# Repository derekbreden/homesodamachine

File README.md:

# Home Soda Machine

A kitchen appliance that dispenses real Pepsi-made diet soda — Diet Mountain Dew, Diet Pepsi, Pepsi Zero Sugar — cold and carbonated, from a faucet. Turn the handle, soda comes out.

The public face of the project is **[homesodamachine.com](https://homesodamachine.com)** — what this is, the 3D viewer, and a single signup form to be notified when units are available. This repository is the working substrate behind that.

The prototype that proves the dispense path is in Derek's kitchen today — a Lilium under-counter carbonator with peristaltic pumps injecting flavor concentrate into the dispensed water. The project's biography lives in [`biography/`](/biography/) — [`2026-04-05.md`](/biography/2026-04-05.md) (origin story: failed SodaStream, the business-license wall, the AI design wall) and [`2026-05-23.md`](/biography/2026-05-23.md) (vision into work: welding, marketing, the engineering).

The product under development is an integrated under-counter soda machine — custom-fabricated 316L stainless carbonator, harvested ice-maker refrigeration loop, foam-insulated cold core, two flavor reservoirs, all behind a single 120 VAC cord and one CO2 line. The machine as it stands, subsystem by subsystem: [`hardware/README.md`](/hardware/README.md). Where it is going and what done looks like: [`future/README.md`](/future/README.md). Who it is for: [`marketing/target-market.md`](/marketing/target-market.md); the cabinet it has to fit: [`marketing/install-envelope.md`](/marketing/install-envelope.md).

## What's where

| Path | Contents |
|---|---|
| [`biography/`](/biography/) | Project biography by chapter — `2026-04-05.md` (founding), `2026-05-23.md` (vision into work) |
| [`hardware/`](/hardware/) | The integrated soda machine under development — CAD scripts, [`bom.md`](/hardware/ledger/bom.md), [`purchases.md`](/hardware/ledger/purchases.md), [`assembly/`](/hardware/assembly/) procedures, printed parts, wiring schedules |
| [`firmware/`](/firmware/) | ESP32 + ESP32-S3 firmware: the main board, the machine display and the faucet display of the soda machine under development, the bare-board bench rig, and the weld rotator — see [`firmware/README.md`](/firmware/README.md) for which tree runs where. |
| [`web/`](/web/) | homesodamachine.com — Node server, CAD viewer — see [`web/README.md`](/web/README.md) |
| [`ios/`](/ios/) | iOS companion app: the BLE link to a machine, firmware updates, pictures, mix, care and settings |
| [`brand/`](brand/README.md) | On tap faucet identity, Big Blue palette, app icons, wordmarks, and shared asset generation |
| [`marketing/`](/marketing/) | Target market analysis, [Lincoln sales and installation](marketing/lincoln/README.md), unboxing brief, video scripts |
| [`business/`](/business/) | Incorporation, regulatory (UL 943, ASSE 1022) |
| [`future/`](/future/) | Where the project is going — the vision and the plan in [`README.md`](/future/README.md), and the desires not yet committed to plans in [`pie-in-the-sky/`](/future/pie-in-the-sky/) |
| [`tools/`](/tools/) | [The `hsm` kernel, build and geometry queries](tools/hsm/README.md), render scripts, printer and bench utilities |

Agents and collaborators landing in this repo: [`CLAUDE.md`](/CLAUDE.md) is the entry point.

## License

MIT

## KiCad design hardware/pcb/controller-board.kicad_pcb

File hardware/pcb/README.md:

# Main board

The main board is a **full PCBA**: JLCPCB-assembled SMD silicon with
through-hole field connectors, no plug-in modules. It lives in
[`pcba/`](/hardware/pcb/pcba/) — `pcba.tsx` is the board, built in
[tscircuit](https://tscircuit.com); see
[`pcba/README.md`](/hardware/pcb/pcba/README.md) for the toolchain and the
render/verify loop.

`pcba.tsx` is the **canonical source of truth for the pin map** — the ESP32 GPIO
assignments and the MCP23017 I²C bank usage (which MCP / port drives which valves
+ condenser fan, and reads which reeds). Those choices are layout-driven and the
board is what gets fabricated, so the wiring diagrams are **derived views kept in
sync with the board**, not the other way round:

- [`esp32-pinout.mmd`](/hardware/wiring/esp32-pinout.mmd) — the ESP32 GPIO map
  (a view of the board).
- [`valve-control.mmd`](/hardware/wiring/valve-control.mmd) — the MCP23017 I²C
  banks (0x20/0x21) and the valve / reed / condenser-fan wiring (a view of the
  board).
- [`ac-wiring-schedule.md`](/hardware/wiring/ac-wiring-schedule.md) — the
  run-by-run field-harness schedule (its own concern, not derived from the pin map).
- [`power.mmd`](/hardware/wiring/power.mmd) — the power topology (likewise).

"Canonical" here means *the single source everyone derives from* — not a claim the
pins are bring-up-validated (they are provisional until the board is tested). A pin
change lands in `pcba.tsx` first, then propagates to these views.

The explicit [`repo-tools check pinmap`](/tools/hsm/repo-tools/src/integrity.rs) reading compares the
canonical pin map from `pcba.tsx` and fails if `esp32-pinout.mmd`, the GPIO constants
of the assembly documents' Rust program, or the BOM disagree — a board pin missing from
the docs, a document's GPIO on the wrong role, or an electrical BOM part with no pad
(the failure that left the piezo buzzer and the MQ-6 gas sensor wired to nothing). Run `repo-tools check pinmap` when reviewing a pin change or preparing a board order. Its exit status reports agreement or drift.

Module part numbers are in [`/hardware/ledger/bom.md`](/hardware/ledger/bom.md) §1.

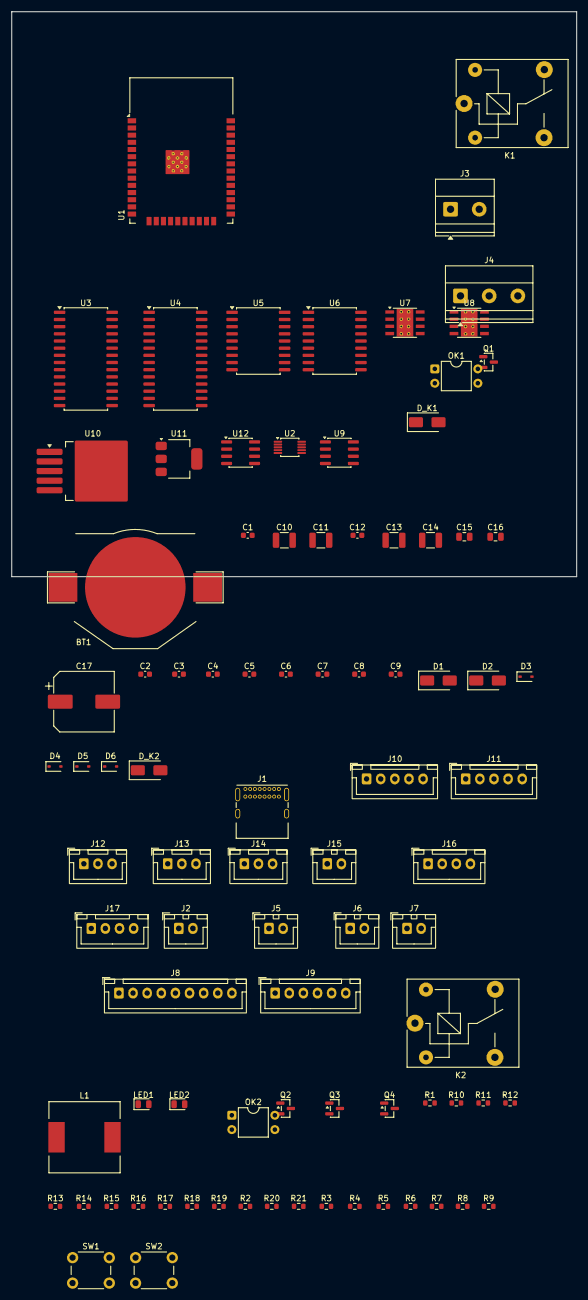
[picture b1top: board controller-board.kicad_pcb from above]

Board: 4 copper layers, 100.0 x 100.0 mm, 89 parts (0 on the bottom side), 91 nets, no tracks yet.

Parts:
BT1: CR2032; BatteryHolder_Keystone_3002_1x2032
C1, C2, C4, C5, C6, C7, C8, C9, C12: 100nF; C_0603_1608Metric
C3: 10uF; C_0603_1608Metric
C10, C11: 100uF; C_1210_3225Metric
C13, C14: 220uF; C_1210_3225Metric
C15, C16: 10uF; C_0805_2012Metric
C17: 470uF; CP_Elec_10x10.5
D1: SMAJ15A; D_SMA
D2: SS14; D_SMA
D3, D4, D5, D6: ESD; D_SOD-323
D_K1, D_K2: SS14; D_SMA
J1: USB_C_Receptacle_USB2.0_16P; USB_C_Receptacle_GCT_USB4085
J2: +12V IN (PSU); JST_XH_B2B-XH-A_1x02_P2.50mm_Vertical
J3: AC IN H/N (fenced); TerminalBlock_Phoenix_MKDS-1,5-2-5.08_1x02_P5.08mm_Horizont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
J4: COMPRESSOR H_sw/N/G; TerminalBlock_Phoenix_MKDS-1,5-3-5.08_1x03_P5.08mm_Horizont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
J5: DIAPHRAGM PUMP 12V; JST_XH_B2B-XH-A_1x02_P2.50mm_Vertical
J6: PUMP U7; JST_XH_B2B-XH-A_1x02_P2.50mm_Vertical
J7: PUMP U8; JST_XH_B2B-XH-A_1x02_P2.50mm_Vertical
J8: VALVES V-A..V-H + 12V; JST_XH_B9B-XH-A_1x09_P2.50mm_Vertical
J9: VALVES V-I..V-K-B + FAN + 12V; JST_XH_B6B-XH-A_1x06_P2.50mm_Vertical
J10: RSVR A reeds; JST_XH_B5B-XH-A_1x05_P2.50mm_Vertical
J11: RSVR B reeds; JST_XH_B5B-XH-A_1x05_P2.50mm_Vertical
J12: CARB reeds lo/hi; JST_XH_B3B-XH-A_1x03_P2.50mm_Vertical
J13: DS18B20 1-wire; JST_XH_B3B-XH-A_1x03_P2.50mm_Vertical
J14: FLOW meter; JST_XH_B3B-XH-A_1x03_P2.50mm_Vertical
J15: BACKFLOW moisture; JST_XH_B2B-XH-A_1x02_P2.50mm_Vertical
J16: CONFIG display RS485; JST_XH_B4B-XH-A_1x04_P2.50mm_Vertical
J17: FAUCET display UART; JST_XH_B4B-XH-A_1x04_P2.50mm_Vertical
K1, K2: Relay_SPDT; Relay_SPDT_SANYOU_SRD_Series_Form_C
L1: 33uH; L_12x12mm_H8mm
LED1: PWR; LED_0805_2012Metric
LED2: STATUS; LED_0805_2012Metric
OK1, OK2: PC817; DIP-4_W7.62mm
Q1, Q2: 2N7002; SOT-23
Q3, Q4: MMBT3904; SOT-23
R1, R2, R6, R7, R8, R18, R20: 10k; R_0603_1608Metric
R3, R4, R5: 4.7k; R_0603_1608Metric
R9, R10, R17, R19: 1k; R_0603_1608Metric
R11, R12: 12k; R_0603_1608Metric
R13, R14: 5.1k; R_0603_1608Metric
R15, R16: 47k; R_0603_1608Metric
R21: 120; R_0603_1608Metric
SW1: BOOT; SW_PUSH_6mm
SW2: EN; SW_PUSH_6mm
U1: ESP32-WROOM-32E; ESP32-WROOM-32
U2: CH340X; MSOP-10_3x3mm_P0.5mm
U3, U4: MCP23017x-x-SO; SOIC-28W_7.5x17.9mm_P1.27mm
U5, U6: ULN2803A; SOIC-18W_7.5x11.6mm_P1.27mm
U7, U8: DRV8871DDA; Texas_HSOP-8-1EP_3.9x4.9mm_P1.27mm_ThermalVias
U9: DS3231MZ; SOIC-8_3.9x4.9mm_P1.27mm
U10: LM2596S-5; TO-263-5_TabPin3
U11: AMS1117-3.3; SOT-223-3_TabPin2
U12: SP3485EN; SOIC-8_3.9x4.9mm_P1.27mm

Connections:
+3V3: C1.1, C2.1, C3.1, C7.1, C8.1, C9.1, C12.1, C16.1, J13.2, R1.1, R2.1, R3.1, R4.1, R5.1, R6.1, R7.1, R10.1, U1.2, U3.9, U3.18, U4.9, U4.15, U4.18, U9.2, U11.2, U12.8
+5V: C14.1, C15.1, D_K1.1, J14.2, J17.3, L1.2, OK1.4, OK2.4, R8.1, U10.4, U11.3
+12V: C10.1, C11.1, C13.1, C17.1, D1.1, D_K2.1, J2.1, J8.9, J9.6, J16.3, U5.10, U6.10, U7.5, U8.5, U10.1
AC_N: J3.2, J4.2
BACKFLOW_MOIST: J15.1, U1.16
CARB_REED_HIGH: J12.2, R7.2, U1.12
CARB_REED_LOW: J12.1, R6.2, U1.28
DTR: Q3.2, R12.1, U2.6
EARTH: J1.SH, J4.3
EN: C4.1, Q3.3, R1.2, SW2.1, U1.3
FLOW_PULSE: D4.1, J14.1, R8.2, U1.37
GND: BT1.2, C1.2, C2.2, C3.2, C4.2, C5.2, C6.2, C7.2, C8.2, C9.2, C10.2, C11.2, C12.2, C13.2, C14.2, C15.2, C16.2, C17.2, D1.2, D2.2, D3.2, D4.2, D5.2, D6.2, J1.A1, J1.A12, J1.B1, J1.B12, J2.2, J5.2, J10.5, J11.5, J12.3, J13.3, J14.3, J15.2, J16.4, J17.4, LED1.1, LED2.1, OK1.2, OK2.2, Q1.2, Q2.2, R13.2, R14.2, R15.2, R16.2, R18.2, R20.2, SW1.2, SW2.2, U1.1, U1.15, U1.38, U1.39, U2.3, U3.10, U3.15, U3.16, U3.17, U4.10, U4.16, U4.17, U5.9, U6.9, U7.1, U7.7, U7.9, U8.1, U8.7, U8.9, U9.5, U10.3, U10.5, U11.1, U12.5
I2C_SCL: R4.2, U1.36, U3.12, U4.12, U9.8
I2C_SDA: R3.2, U1.33, U3.13, U4.13, U9.7
IO0_BOOT: Q4.3, R2.2, SW1.1, U1.25
K1_GATE: OK1.3, Q1.1, R18.1
K2_GATE: OK2.3, Q2.1, R20.1
unnamed: LED2.2, R9.2
unnamed: LED1.2, R10.2
unnamed: C6.1, U2.10
unnamed: Q3.1, R11.2
unnamed: Q4.1, R12.2
unnamed: J1.A5, R13.1
unnamed: J1.B5, R14.1
unnamed: U3.21, U5.1
unnamed: U3.22, U5.2
unnamed: U3.23, U5.3
unnamed: U3.24, U5.4
unnamed: U3.25, U5.5
unnamed: U3.26, U5.6
unnamed: U3.27, U5.7
unnamed: U3.28, U5.8
unnamed: U3.1, U6.1
unnamed: U3.2, U6.2
unnamed: U3.3, U6.3
unnamed: U3.4, U6.4
unnamed: U4.25, U6.5
unnamed: J8.1, U5.18
unnamed: J8.2, U5.17
unnamed: J8.3, U5.16
unnamed: J8.4, U5.15
unnamed: J8.5, U5.14
unnamed: J8.6, U5.13
unnamed: J8.7, U5.12
unnamed: J8.8, U5.11
unnamed: J9.1, U6.18
unnamed: J9.2, U6.17
unnamed: J9.3, U6.16
unnamed: J9.4, U6.15
unnamed: J9.5, U6.14
unnamed: R15.1, U7.4
unnamed: J6.1, U7.6
unnamed: J6.2, U7.8
unnamed: R16.1, U8.4
unnamed: J7.1, U8.6
unnamed: J7.2, U8.8
unnamed: OK1.1, R17.2
unnamed: D_K1.2, Q1.3
unnamed: OK2.1, R19.2
unnamed: D_K2.2, Q2.3
ONEWIRE: D3.1, J13.1, R5.2, U1.27
PUMP_A_IN1: U1.10, U7.3
PUMP_A_IN2: U1.11, U7.2
PUMP_B_IN1: U1.30, U8.3
PUMP_B_IN2: U1.29, U8.2
RELAY1_DRIVE: R17.1, U1.13
RELAY2_DRIVE: R19.1, U1.26
RS485_A: J16.1, R21.1, U12.6
RS485_B: J16.2, R21.2, U12.7
RS485_DE: U1.9, U12.2, U12.3
RSVR_A_REED1: J10.1, U3.5
RSVR_A_REED2: J10.2, U3.6
RSVR_A_REED3: J10.3, U3.7
RSVR_A_REED4: J10.4, U3.8
RSVR_B_REED1: J11.1, U4.21
RSVR_B_REED2: J11.2, U4.22
RSVR_B_REED3: J11.3, U4.23
RSVR_B_REED4: J11.4, U4.24
RTS: Q4.2, R11.1, U2.4
RXD0: U1.34, U2.8
STATUS_LED: R9.1, U1.24
SW_5V: D2.1, L1.1, U10.2
TXD0: U1.35, U2.9
UART1_RX: U1.6, U12.1
UART1_TX: U1.23, U12.4
UART2_RX: D6.1, J17.2, U1.7
UART2_TX: D5.1, J17.1, U1.8
USB_D+: J1.A6, J1.B6, U2.1
USB_D-: J1.A7, J1.B7, U2.2
VBAT: BT1.1, U9.6
VBUS: C5.1, J1.A4, J1.A9, J1.B4, J1.B9, U2.7

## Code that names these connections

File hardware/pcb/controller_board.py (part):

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u1rx    = espnet("UART1_RX", "IO34")
u2tx    = espnet("UART2_TX", "IO32")
u2rx    = espnet("UART2_RX", "IO35")
rs485_de = espnet("RS485_DE", "IO33")          # freed pin -> SP3485 DE/~RE
backflow = espnet("BACKFLOW_MOIST", "IO13")    # decision #2
txd0    = espnet("TXD0", "TXD0/IO1")
rxd0    = espnet("RXD0", "RXD0/IO3")
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k1 = relay_drive("K1", "Q1", "OK1", rly1, p5, ac_hot, ac_sw)     # 5V coil
j_ac_in = conn("J3", 2, "AC IN H/N (fenced)",
               "TerminalBlock_Phoenix:TerminalBlock_Phoenix_MKDS-1,5-2-5.08_1x02_P5.08mm_Horizontal")
wire(ac_hot, pn(j_ac_in, "Pin_1")); wire(ac_n, pn(j_ac_in, "Pin_2"))
j_ac_comp = conn("J4", 3, "COMPRESSOR H_sw/N/G",
                 "TerminalBlock_Phoenix:TerminalBlock_Phoenix_MKDS-1,5-3-5.08_1x03_P5.08mm_Horizontal")
wire(ac_sw, pn(j_ac_comp, "Pin_1")); wire(ac_n, pn(j_ac_comp, "Pin_2"))
wire(earth, pn(j_ac_comp, "Pin_3"))

dia_sw = Net("DIAPHRAGM_12V_SW")
k2 = relay_drive("K2", "Q2", "OK2", rly2, p12, p12, dia_sw)      # 12V coil
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j_carb = jst("J12", 3, "CARB reeds lo/hi")
wire(carb_lo, pn(j_carb, "Pin_1")); wire(carb_hi, pn(j_carb, "Pin_2")); wire(gnd, pn(j_carb, "Pin_3"))
j_ow = jst("J13", 3, "DS18B20 1-wire")
wire(onewire, pn(j_ow, "Pin_1")); wire(p3v3, pn(j_ow, "Pin_2")); wire(gnd, pn(j_ow, "Pin_3"))
j_flow = jst("J14", 3, "FLOW meter")
wire(flow, pn(j_flow, "Pin_1")); wire(p5, pn(j_flow, "Pin_2")); wire(gnd, pn(j_flow, "Pin_3"))
j_back = jst("J15", 2, "BACKFLOW moisture")
wire(backflow, pn(j_back, "Pin_1")); wire(gnd, pn(j_back, "Pin_2"))
j_cfg = jst("J16", 4, "CONFIG display RS485")
wire(rs485_a, pn(j_cfg, "Pin_1")); wire(rs485_b, pn(j_cfg, "Pin_2"))
wire(p12, pn(j_cfg, "Pin_3")); wire(gnd, pn(j_cfg, "Pin_4"))
j_fau = jst("J17", 4, "FAUCET display UART")
wire(u2tx, pn(j_fau, "Pin_1")); wire(u2rx, pn(j_fau, "Pin_2"))
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pn(l1, "2").drive = POWER              # +5V (buck inductor output)
pn(usbc, "VBUS")[0].drive = POWER      # VBUS
pn(bt, "+").drive = POWER              # VBAT
pn(j_ac_comp, "Pin_3").drive = POWER   # EARTH


def noconn(part, *keys):
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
